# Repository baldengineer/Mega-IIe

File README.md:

# Golden Delicious
This project started as a portable Apple ][ by using the Mega-II chip from an IIGS. (This chip is precursor, and slightly different to the Gemini in the Mac LC compatibility card.) However, it evolved into making a miniture Apple IIe compatible computer.

This repo contains the KiCad design files, RP2040 firmware, and notes for the Mega IIe computer. 

## Rev 3 Video
This element14 Presents video documents the effort to get from an Applesoft Prompt to a fully functional computer, in a miniature case.

https://www.youtube.com/watch?v=gFCD4s_hsb4

You can find additional information on the [element14 Community](https://bald.ee/e14-megaiie) or in this [Hackster.io](https://www.hackster.io/news/bald-engineer-s-mega-iie-is-a-modern-miniature-apple-ii-based-on-mega-ii-chip-from-1986-019507d4d10c) article. 

## Bit Preserve
This project is why I started [Bit Preserve](https://github.com/baldengineer/bit-preserve), a project to archive vintage computer schematics.

# Notes
When live streaming the probject, I kept some notes here for future reference.

## (Off-)Stream Notes 2021-10-02
* Attempting to book the GD with a IIc ROM results in a lock-up.
  * graphics get initialized and the memory is dumped to the screen, but no beep and nothing past that.
  * Logic Analyzer suggests `BASICINIT` is doing a monitor version check in the F8 ROM, but failing. It calls a jump called `HANG`. Even though the 6502 should be jumping in a circle, it seems to keep doing other stuff. (Maybe it is just bus fetches that do nothing?)
* SLOTMAKER Bus Headers on the IO board are pinned out different from the SLOTMAKER Bus Header on the MEGA-65c02. For a ribbon cable, each pin-pair needs to be swapped, except for the last two. They are GND.

## Stream Notes 2021-10-01
Golden Delicious Rev 2 booted! Yay!

* \~DMA is wrong level
  * The two \`245 buffers have their enable pins connnected to \~DMA. I made the mistake of thinking that MEGA drove the \~DMA signal. That is not the case, nor does it make sense after thinking about it. For now, the \`245s have pin 19 lifted and tied to ground to always enable them. 
  * When connecting the IWM or a card to slotmaker, \~DMA situation needs to be resolved.

* [IIe / 6502 decoder](https://discord.com/channels/369243434080272385/843878836471201902/893914917676130314) for Waveforms / Digitial Discovery has been updated. 
* This [forum post](https://discord.com/channels/369243434080272385/843878836471201902/893915436620607488) has Digilent Waveforms beta builds that are downloadable without filling out the annoying registration form. (Or just use `asdf` for all of the fields.)

## Stream Notes 2021-06-02
* Wherefore no IIe ROM in the IIgs? Is it in the MEGA-II?
* [Warphammer: this seciton looks rommy](https://twitter.com/babbageboole/status/1001178057057566720/photo/1)
* rjhelms: that's the big question mark - there could be logic in the Mega II that never actually gets used because the CYA is doing it all in this implementation
* al: keep it all breakouts
* can we decode ROMEN1 and ROMEN2 ourselves?

## Stream Notes 2021-05-19
Things to look at on the scope:
* Composite signal out of the Mega II
* What is Mono-Color from VGC doing to Chroma into MC1377
* Is VGC refreshing apple II DRAM (or is it the Mega)
* why is the 28 MHz oscillator enabled/disabled from the VGC's !SYNC pin?
* [PLCC Pinout Page](https://www.sbprojects.net/knowledge/footprints/plcc/index.php)

### Renesas / IDT OSC: XLH735028.636360I 
* XL H 7 3 5 0 28.636360 I 
  * XL = 1,000,000 af
  * H = LVCMOS En/Dis Pin 1
  * 7 = 7.0 x 5.0 mm
  * 3 = 3.3 VDC
  * 5 = 100ppm for -40C to 105C only on tuesdays when the moon is full and it hasn't rained for a few days. also if you ate green skittles recently *Note1*

### BoM for Protoboards
* [Possible MC1377 Source](https://www.ebay.com/itm/192523168043?hash=item2cd346692b:g:BgIAAOSwWfda4kj6)

## Stream Notes 2021-05-16
* [WDC Application note on using 65C02 in Apple II and other old systems](https://www.westerndesigncenter.com/wdc/AN-002_W65C02S_Replacements.php)
* [65C02 Datasheet](https://www.westerndesigncenter.com/wdc/documentation/w65c02s.pdf)

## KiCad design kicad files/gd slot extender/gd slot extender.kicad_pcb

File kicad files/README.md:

## Golden Delicious KiCad Files

The Proto PCBs are boards to prototype an IIe from the IIgs ASICs. Eventually, these will be condensed to a single board.

### gd 6502 proto pcb
6502 board is designed for a WDC W65c02 with a QFP footprint. It has a single socket for an EPROM and is wired like the IIc's EEPROM. The `Address` and `Data` headers are meant to connect to the MEGA-II proto board. Other control signals are broken out to other headers.

Runs off of 5V.

### gd MegaII proto pcb
This board is the center piece. It contains the MEGA-II and has all of its signals broken out to multiple headers. 

It connects to both the VGC and 6502 boards. The VGC connects with a 40-pin cable, like an IDE cable. The 6502 connects with a couple of ribbon cables.

Runs off of 5V.

### gd VGC proto pcb
First board to be finished and the one with the least use for the final handheld. The VGC converts the RGB bitstream from the MEGA-II into an analog signal and then into NTSC.

The VGC also generates the 14 MHz clock from a 28 MHz oscilliator. (It is not clear yet which clocks the MEGA-II generates and which the VGC does.)

Runs off of +5V, -5V, and +12V. The 12V and -5V are used by the NTSC generation circuit.

### KiCad_Symbols
Late in the board creation process, I tried to consoliate the symbols into one location. These symbols and these boards are based off of the ROM3 IIgs schematic in [Bit Preserve](https://github.com/baldengineer/bit-preserve).

### MegaII Breakout
Very old breakout board. Created that and realized it wasn't very useful by itself.

## Live Stream
This entire project has been livestreamed on [Bald Engineer Live](https://twitch.tv/baldengineer).

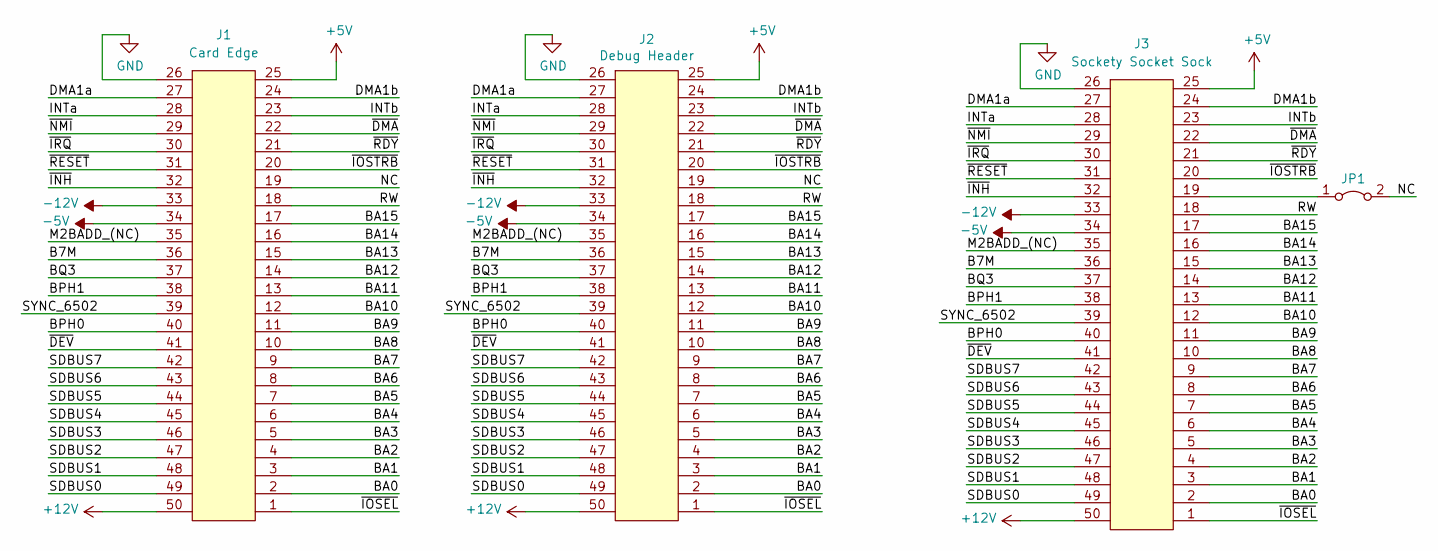
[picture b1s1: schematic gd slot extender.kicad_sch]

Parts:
J1: Card Edge; AppleIIBus
J2: Debug Header; PinHeader_2x25_P2.54mm_Vertical
J3: Sockety Socket Sock; Amp_2358256-4_50pos_right_angle_card
JP1: Jumper_2_Bridged; SolderJumper-2_P1.3mm_Bridged_RoundedPad1.0x1.5mm

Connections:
+5V: J1.25, J2.25, J3.25
+12V: J1.50, J2.50, J3.50
-5V: J1.34, J2.34, J3.34
-12V: J1.33, J2.33, J3.33
/B7M: J1.36, J2.36, J3.36
/BA0: J1.2, J2.2, J3.2
/BA1: J1.3, J2.3, J3.3
/BA2: J1.4, J2.4, J3.4
/BA3: J1.5, J2.5, J3.5
/BA4: J1.6, J2.6, J3.6
/BA5: J1.7, J2.7, J3.7
/BA6: J1.8, J2.8, J3.8
/BA7: J1.9, J2.9, J3.9
/BA8: J1.10, J2.10, J3.10
/BA9: J1.11, J2.11, J3.11
/BA10: J1.12, J2.12, J3.12
/BA11: J1.13, J2.13, J3.13
/BA12: J1.14, J2.14, J3.14
/BA13: J1.15, J2.15, J3.15
/BA14: J1.16, J2.16, J3.16
/BA15: J1.17, J2.17, J3.17
/BPH0: J1.40, J2.40, J3.40
/BPH1: J1.38, J2.38, J3.38
/BQ3: J1.37, J2.37, J3.37
/DMA1a: J1.27, J2.27, J3.27
/DMA1b: J1.24, J2.24, J3.24
/INTa: J1.28, J2.28, J3.28
/INTb: J1.23, J2.23, J3.23
/M2BADD_(NC): J1.35, J2.35, J3.35
/NC: J1.19, J2.19, JP1.2 (B)
/RW: J1.18, J2.18, J3.18
/SDBUS0: J1.49, J2.49, J3.49
/SDBUS1: J1.48, J2.48, J3.48
/SDBUS2: J1.47, J2.47, J3.47
/SDBUS3: J1.46, J2.46, J3.46
/SDBUS4: J1.45, J2.45, J3.45
/SDBUS5: J1.44, J2.44, J3.44
/SDBUS6: J1.43, J2.43, J3.43
/SDBUS7: J1.42, J2.42, J3.42
/SYNC_6502: J1.39, J2.39, J3.39
/~DEV: J1.41, J2.41, J3.41
/~DMA: J1.22, J2.22, J3.22
/~INH: J1.32, J2.32, J3.32
/~IOSEL: J1.1, J2.1, J3.1
/~IOSTRB: J1.20, J2.20, J3.20
/~IRQ: J1.30, J2.30, J3.30
/~NMI: J1.29, J2.29, J3.29
/~RDY: J1.21, J2.21, J3.21
/~RESET: J1.31, J2.31, J3.31
GND: J1.26, J2.26, J3.26
unnamed: J3.19, JP1.1 (A)

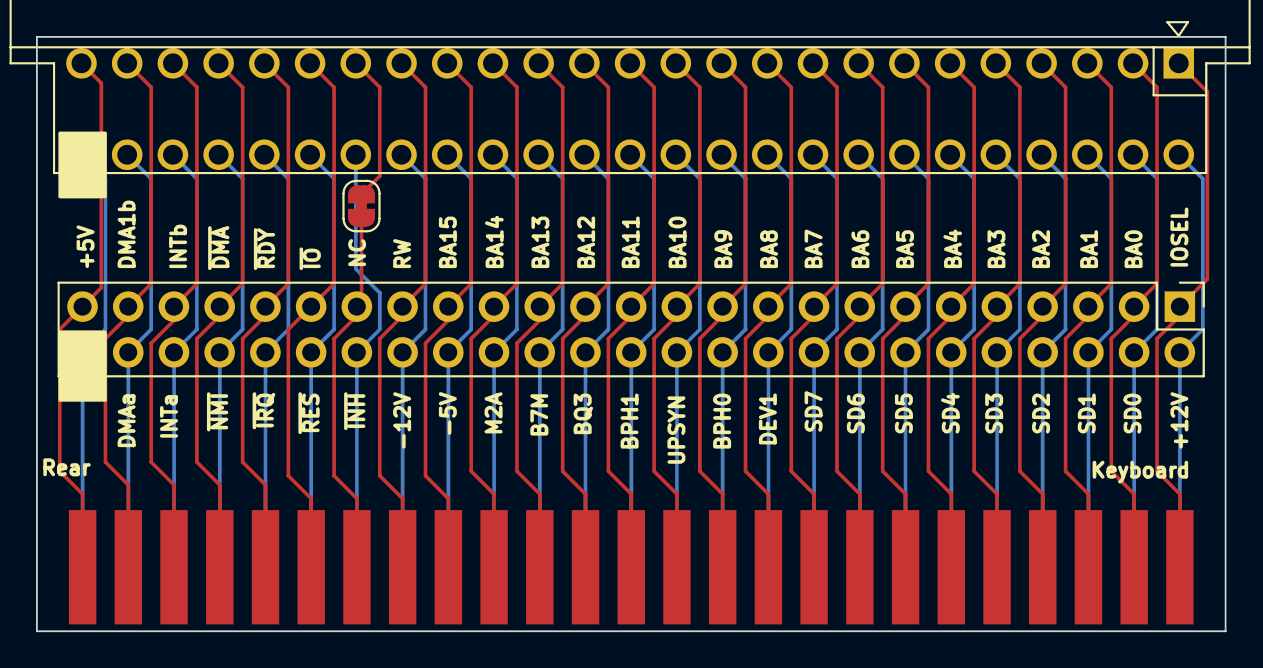
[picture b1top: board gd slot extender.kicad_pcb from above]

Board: 2 copper layers, 66.0 x 33.0 mm, 4 parts (0 on the bottom side), 51 nets.

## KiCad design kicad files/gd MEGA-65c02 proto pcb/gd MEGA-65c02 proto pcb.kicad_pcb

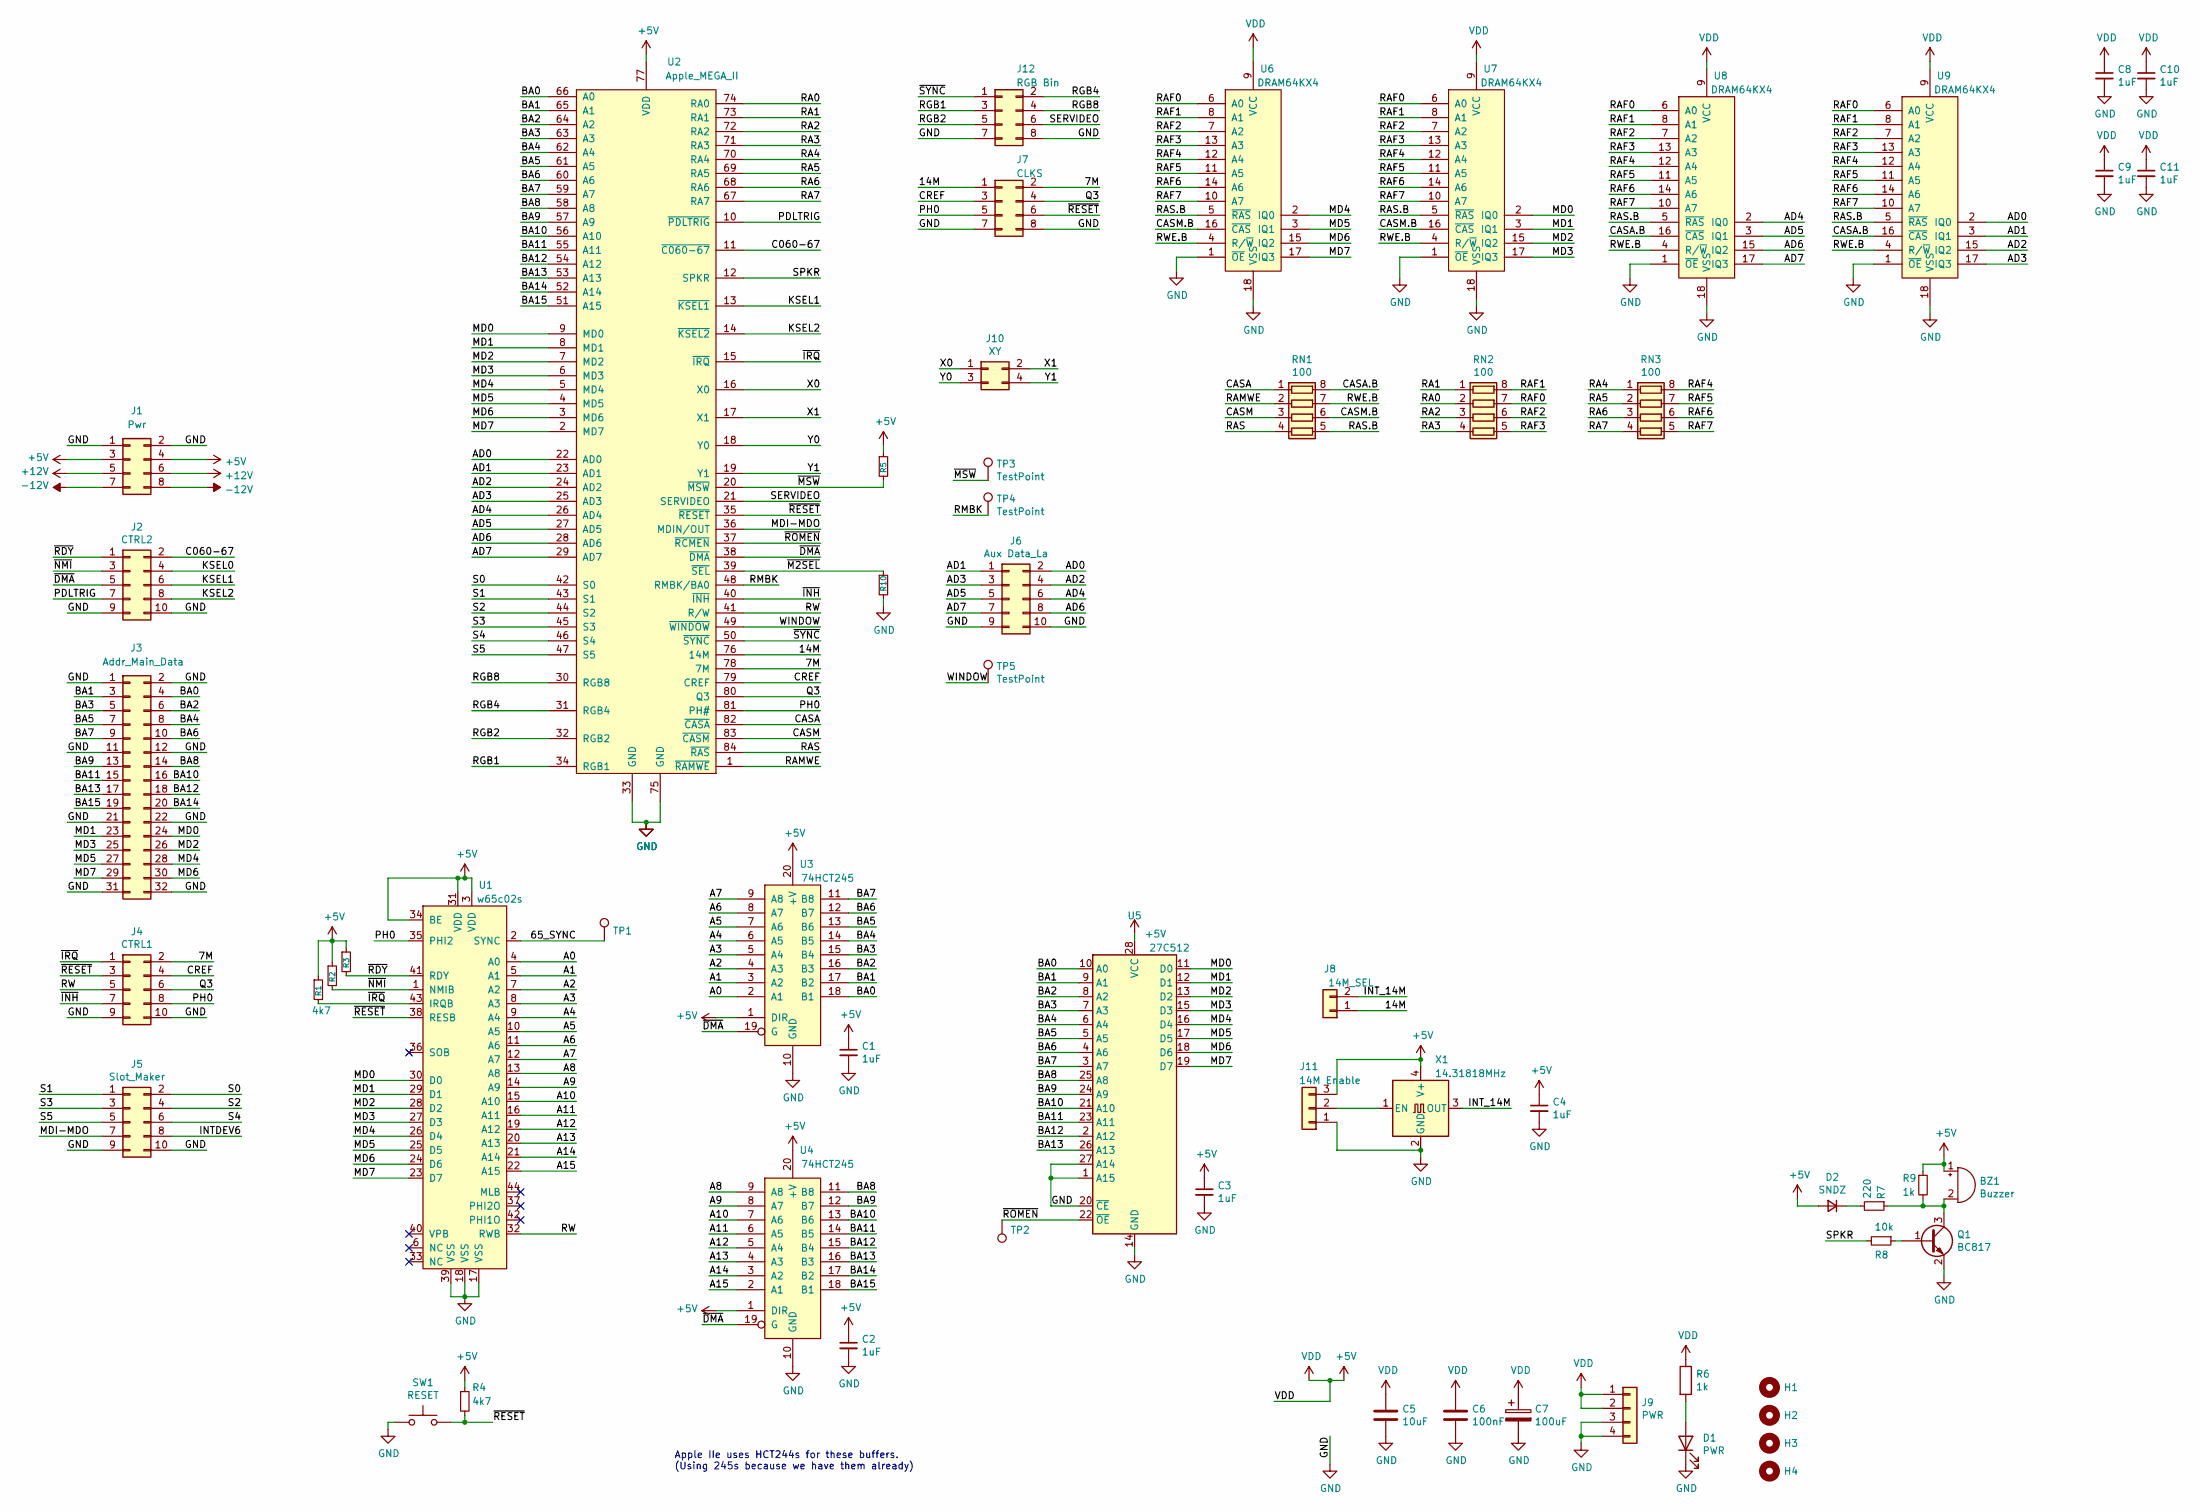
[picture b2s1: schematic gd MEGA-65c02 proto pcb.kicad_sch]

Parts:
BZ1: Buzzer; 12mm_Piezo_Buzzer
C1, C2, C3, C4, C8, C9, C10, C11: 1uF; C_0805_2012Metric
C5: 10uF; C_0805_2012Metric
C6: 100nF; C_0805_2012Metric
C7: 100uF; CP_EIA-3216-18_Kemet-A_Pad1.58x1.35mm_HandSolder
D1: PWR; LED_1206_3216Metric
D2: SNDZ; LED_1206_3216Metric
H1, H2, H3, H4: MountingHole; MountingHole_2.5mm
J1: Pwr; PinHeader_2x04_P2.54mm_Vertical-NOSILK
J2: CTRL2; PinHeader_2x05_P2.54mm_Vertical
J3: Addr_Main_Data; PinHeader_2x16_P2.54mm_Vertical
J4: CTRL1; PinHeader_2x05_P2.54mm_Vertical
J5: Slot_Maker; PinHeader_2x05_P2.54mm_Vertical
J6: Aux Data_La; PinHeader_2x05_P2.54mm_Vertical
J7: CLKS; PinHeader_2x04_P2.54mm_Vertical
J8: 14M_SEL; PinHeader_1x02_P2.54mm_Vertical
J9: PWR; PinHeader_1x04_P2.54mm_Vertical
J10: XY; PinHeader_2x02_P2.54mm_Vertical
J11: 14M Enable; PinHeader_1x03_P2.54mm_Vertical
J12: RGB Bin; PinHeader_2x04_P2.54mm_Vertical
Q1: BC817; SOT-23
R1, R4, R5, R10: 4k7; R_0805_2012Metric
R2, R3: 3k3; R_0805_2012Metric
R6, R9: 1k; R_0805_2012Metric
R7: 220; R_0805_2012Metric
R8: 10k; R_0805_2012Metric
RN1, RN2, RN3: 100; R_Array_Convex_4x0612
SW1: RESET; SW_Push_1P1T_NO_CK_KSC6xxJ
TP1, TP2: TestPoint_Harwin; Harwin-S1751-46-Test-Point
TP3, TP4, TP5: TestPoint; Harwin-S1751-46-Test-Point
U1: w65c02s; TQFP-44_10x10mm_P0.8mm
U2: Apple_MEGA_II; PLCC-84_THT-Socket
U3, U4: 74HCT245; SOIC-20W_7.5x12.8mm_P1.27mm
U5: 27C512; DIP_Socket-28_W11.9_W12.7_W15.24_W17.78_W18.5_3M_228-1277-0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
U6, U7, U8, U9: DRAM64KX4; DIP-18_W7.62mm_Socket_LongPads
X1: 14.31818MHz; Oscillator_SMD_SeikoEpson_SG8002CA-4Pin_7.0x5.0mm_HandSolde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; MPN MCSJK-6NC1-14.31818-25-B

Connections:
+5V: BZ1.1 (-), C1.1, C2.1, C3.1, C4.1, C5.1, C6.1, C7.1, C8.1, C9.1, C10.1, C11.1, D2.2 (A), J1.3, J1.4, J9.1, J9.2, J11.3, R1.1, R2.1, R3.1, R4.1, R5.1, R6.1, R9.1, U1.3 (VDD), U1.31 (VDD), U1.34 (BE), U2.77 (VDD), U3.1 (DIR), U3.20 (+V), U4.1 (DIR), U4.20 (+V), U5.28 (VCC), U6.9 (VCC), U7.9 (VCC), U8.9 (VCC), U9.9 (VCC), X1.4 (V+)
+12V: J1.5, J1.6
-12V: J1.7, J1.8
/7M: J4.2, J7.2, U2.78 (7M)
/14M: J7.1, J8.1, U2.76 (14M)
/65_SYNC: TP1.1, U1.2 (SYNC)
/A0: U1.4 (A0), U3.2 (A1)
/A1: U1.5 (A1), U3.3 (A2)
/A2: U1.7 (A2), U3.4 (A3)
/A3: U1.8 (A3), U3.5 (A4)
/A4: U1.9 (A4), U3.6 (A5)
/A5: U1.10 (A5), U3.7 (A6)
/A6: U1.11 (A6), U3.8 (A7)
/A7: U1.12 (A7), U3.9 (A8)
/A8: U1.13 (A8), U4.9 (A8)
/A9: U1.14 (A9), U4.8 (A7)
/A10: U1.15 (A10), U4.7 (A6)
/A11: U1.16 (A11), U4.6 (A5)
/A12: U1.19 (A12), U4.5 (A4)
/A13: U1.20 (A13), U4.4 (A3)
/A14: U1.21 (A14), U4.3 (A2)
/A15: U1.22 (A15), U4.2 (A1)
/AD0: J6.2, U2.22 (AD0), U9.2 (IQ0)
/AD1: J6.1, U2.23 (AD1), U9.3 (IQ1)
/AD2: J6.4, U2.24 (AD2), U9.15 (IQ2)
/AD3: J6.3, U2.25 (AD3), U9.17 (IQ3)
/AD4: J6.6, U2.26 (AD4), U8.2 (IQ0)
/AD5: J6.5, U2.27 (AD5), U8.3 (IQ1)
/AD6: J6.8, U2.28 (AD6), U8.15 (IQ2)
/AD7: J6.7, U2.29 (AD7), U8.17 (IQ3)
/BA0: J3.4, U2.66 (A0), U3.18 (B1), U5.10 (A0)
/BA1: J3.3, U2.65 (A1), U3.17 (B2), U5.9 (A1)
/BA2: J3.6, U2.64 (A2), U3.16 (B3), U5.8 (A2)
/BA3: J3.5, U2.63 (A3), U3.15 (B4), U5.7 (A3)
/BA4: J3.8, U2.62 (A4), U3.14 (B5), U5.6 (A4)
/BA5: J3.7, U2.61 (A5), U3.13 (B6), U5.5 (A5)
/BA6: J3.10, U2.60 (A6), U3.12 (B7), U5.4 (A6)
/BA7: J3.9, U2.59 (A7), U3.11 (B8), U5.3 (A7)
/BA8: J3.14, U2.58 (A8), U4.11 (B8), U5.25 (A8)
/BA9: J3.13, U2.57 (A9), U4.12 (B7), U5.24 (A9)
/BA10: J3.16, U2.56 (A10), U4.13 (B6), U5.21 (A10)
/BA11: J3.15, U2.55 (A11), U4.14 (B5), U5.23 (A11)
/BA12: J3.18, U2.54 (A12), U4.15 (B4), U5.2 (A12)
/BA13: J3.17, U2.53 (A13), U4.16 (B3), U5.26 (A13)
/BA14: J3.20, U2.52 (A14), U4.17 (B2)
/BA15: J3.19, U2.51 (A15), U4.18 (B1)
/C060-67: J2.2, U2.11 (~C060-67)
/CASA: RN1.1 (R1.1), U2.82 (~CASA)
/CASA.B: RN1.8 (R1.2), U8.16 (~CAS), U9.16 (~CAS)
/CASM: RN1.3 (R3.1), U2.83 (~CASM)
/CASM.B: RN1.6 (R3.2), U6.16 (~CAS), U7.16 (~CAS)
/CREF: J4.4, J7.3, U2.79 (CREF)
/INTDEV6: J5.8
/INT_14M: J8.2, X1.3 (OUT)
/KSEL0: J2.4
/KSEL1: J2.6, U2.13 (~KSEL1)
/KSEL2: J2.8, U2.14 (~KSEL2)
/MD0: J3.24, U1.30 (D0), U2.9 (MD0), U5.11 (D0), U7.2 (IQ0)
/MD1: J3.23, U1.29 (D1), U2.8 (MD1), U5.12 (D1), U7.3 (IQ1)
/MD2: J3.26, U1.28 (D2), U2.7 (MD2), U5.13 (D2), U7.15 (IQ2)
/MD3: J3.25, U1.27 (D3), U2.6 (MD3), U5.15 (D3), U7.17 (IQ3)
/MD4: J3.28, U1.26 (D4), U2.5 (MD4), U5.16 (D4), U6.2 (IQ0)
/MD5: J3.27, U1.25 (D5), U2.4 (MD5), U5.17 (D5), U6.3 (IQ1)
/MD6: J3.30, U1.24 (D6), U2.3 (MD6), U5.18 (D6), U6.15 (IQ2)
/MD7: J3.29, U1.23 (D7), U2.2 (MD7), U5.19 (D7), U6.17 (IQ3)
/MDI-MDO: J5.7, U2.36 (MDIN/OUT)
/PDLTRIG: J2.7, U2.10 (~PDLTRIG)
/PH0: J4.8, J7.5, U1.35 (PHI2), U2.81 (PH#)
/Q3: J4.6, J7.4, U2.80 (Q3)
/RA0: RN2.2 (R2.1), U2.74 (RA0)
/RA1: RN2.1 (R1.1), U2.73 (RA1)
/RA2: RN2.3 (R3.1), U2.72 (RA2)
/RA3: RN2.4 (R4.1), U2.71 (RA3)
/RA4: RN3.1 (R1.1), U2.70 (RA4)
/RA5: RN3.2 (R2.1), U2.69 (RA5)
/RA6: RN3.3 (R3.1), U2.68 (RA6)
/RA7: RN3.4 (R4.1), U2.67 (RA7)
/RAF0: RN2.7 (R2.2), U6.6 (A0), U7.6 (A0), U8.6 (A0), U9.6 (A0)
/RAF1: RN2.8 (R1.2), U6.8 (A1), U7.8 (A1), U8.8 (A1), U9.8 (A1)
/RAF2: RN2.6 (R3.2), U6.7 (A2), U7.7 (A2), U8.7 (A2), U9.7 (A2)
/RAF3: RN2.5 (R4.2), U6.13 (A3), U7.13 (A3), U8.13 (A3), U9.13 (A3)
/RAF4: RN3.8 (R1.2), U6.12 (A4), U7.12 (A4), U8.12 (A4), U9.12 (A4)
/RAF5: RN3.7 (R2.2), U6.11 (A5), U7.11 (A5), U8.11 (A5), U9.11 (A5)
/RAF6: RN3.6 (R3.2), U6.14 (A6), U7.14 (A6), U8.14 (A6), U9.14 (A6)
/RAF7: RN3.5 (R4.2), U6.10 (A7), U7.10 (A7), U8.10 (A7), U9.10 (A7)
/RAMWE: RN1.2 (R2.1), U2.1 (~RAMWE)
/RAS: RN1.4 (R4.1), U2.84 (~RAS)
/RAS.B: RN1.5 (R4.2), U6.5 (~RAS), U7.5 (~RAS), U8.5 (~RAS), U9.5 (~RAS)
/RGB1: J12.3, U2.34 (RGB1)
/RGB2: J12.5, U2.32 (RGB2)
/RGB4: J12.2, U2.31 (RGB4)
/RGB8: J12.4, U2.30 (RGB8)
/RMBK: TP4.1, U2.48 (RMBK/BA0)
/RW: J4.5, U1.32 (RWB), U2.41 (R/W)
/RWE.B: RN1.7 (R2.2), U6.4 (R/~W), U7.4 (R/~W), U8.4 (R/~W), U9.4 (R/~W)
/S0: J5.2, U2.42 (S0)
/S1: J5.1, U2.43 (S1)
/S2: J5.4, U2.44 (S2)
/S3: J5.3, U2.45 (S3)
/S4: J5.6, U2.46 (S4)
/S5: J5.5, U2.47 (S5)
/SERVIDEO: J12.6, U2.21 (SERVIDEO)
/SPKR: R8.2, U2.12 (SPKR)
/WINDOW: TP5.1, U2.49 (~WINDOW)
/X0: J10.1, U2.16 (X0)
/X1: J10.2, U2.17 (X1)
/Y0: J10.3, U2.18 (Y0)
/Y1: J10.4, U2.19 (Y1)
/~DMA: J2.5, U2.38 (~DMA), U3.19 (G), U4.19 (G)
/~INH: J4.7, U2.40 (~INH)
/~IRQ: J4.1, R1.2, U1.43 (IRQB), U2.15 (~IRQ)
/~M2SEL: R10.1, U2.39 (~SEL)
/~MSW: R5.2, TP3.1, U2.20 (~MSW)
/~NMI: J2.3, R2.2, U1.1 (NMIB)
/~RDY: J2.1, R3.2, U1.41 (RDY)
/~RESET: J4.3, J7.6, R4.2, SW1.2, U1.38 (RESB), U2.35 (~RESET)
/~ROMEN: TP2.1, U2.37 (~RCMEN), U5.22 (~OE)
/~SYNC: J12.1, U2.50 (~SYNC)
GND: C1.2, C2.2, C3.2, C4.2, C5.2, C6.2, C7.2, C8.2, C9.2, C10.2, C11.2, D1.1 (K), J1.1, J1.2, J2.9, J2.10, J3.1, J3.2, J3.11, J3.12, J3.21, J3.22, J3.31, J3.32, J4.9, J4.10, J5.9, J5.10, J6.9, J6.10, J7.7, J7.8, J9.3, J9.4, J11.1, J12.7, J12.8, Q1.2 (E), R10.2, SW1.1, U1.17 (VSS), U1.18 (VSS), U1.39 (VSS), U2.33 (GND), U2.75 (GND), U3.10 (GND), U4.10 (GND), U5.1 (A15), U5.14 (GND), U5.20 (~CE), U5.27 (A14), U6.1 (~OE), U6.18 (VSS), U7.1 (~OE), U7.18 (VSS), U8.1 (~OE), U8.18 (VSS), U9.1 (~OE), U9.18 (VSS), X1.2 (GND)
unnamed: BZ1.2 (+), Q1.3 (C), R7.1, R9.2
unnamed: D1.2 (A), R6.2
unnamed: D2.1 (K), R7.2
unnamed: J11.2, X1.1 (EN)
unnamed: Q1.1 (B), R8.1

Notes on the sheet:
Apple IIe uses HCT244s for these buffers. (Using 245s because we have them already)

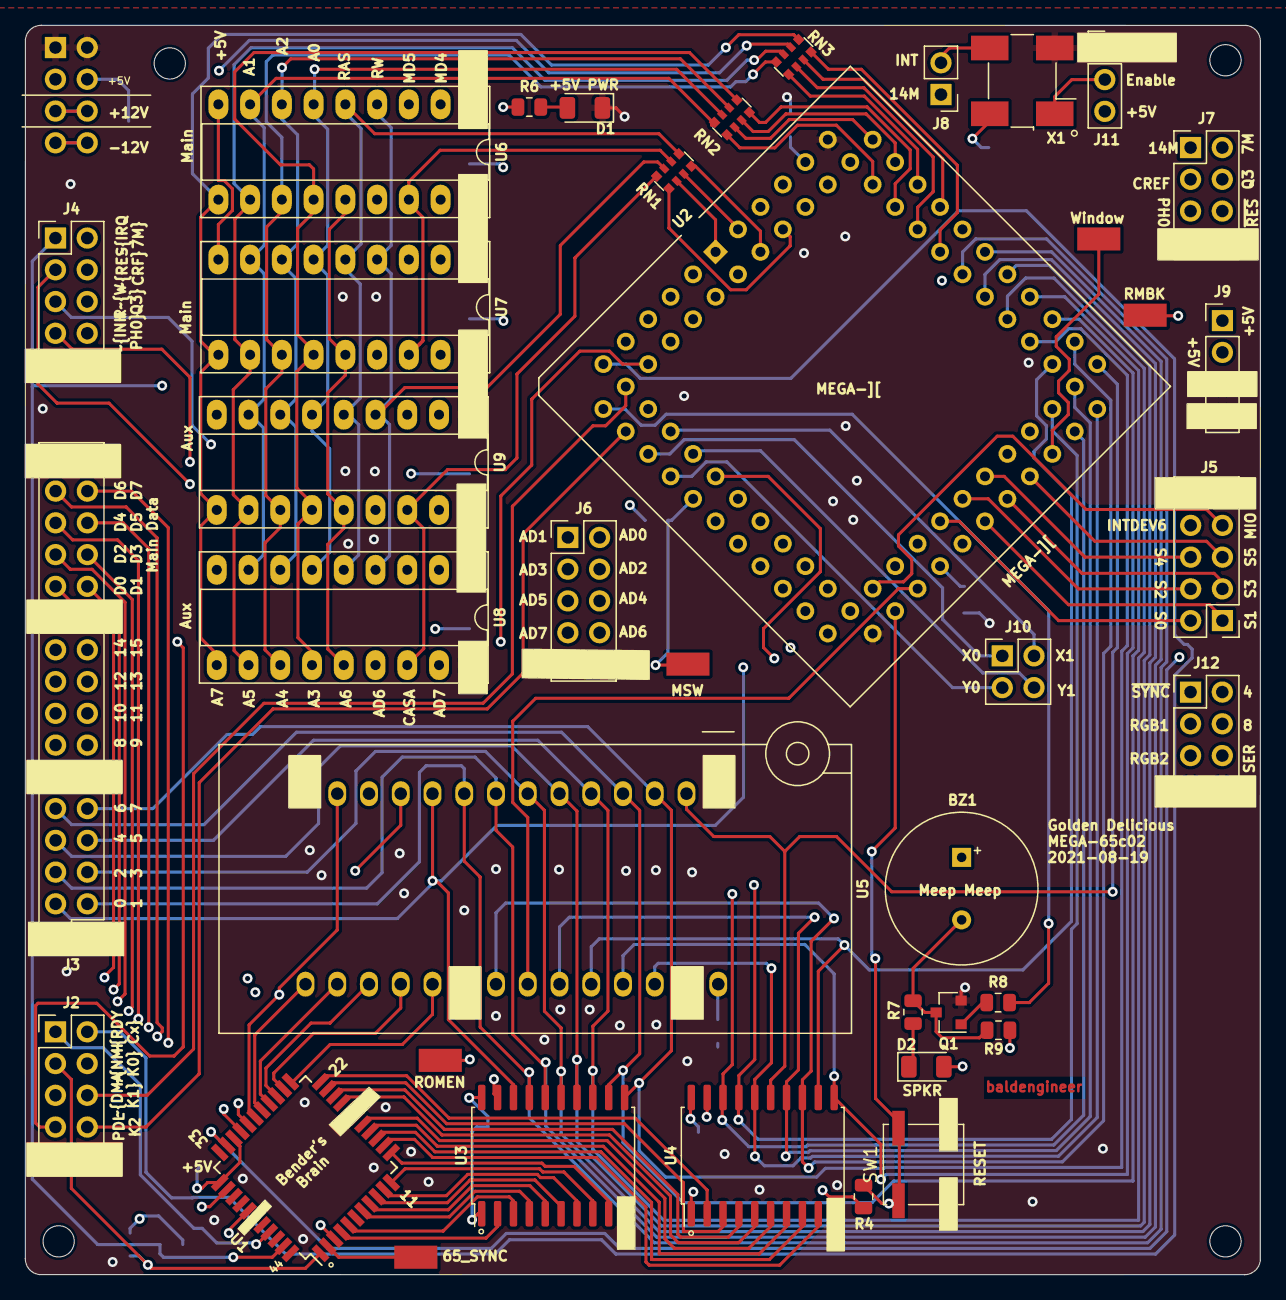
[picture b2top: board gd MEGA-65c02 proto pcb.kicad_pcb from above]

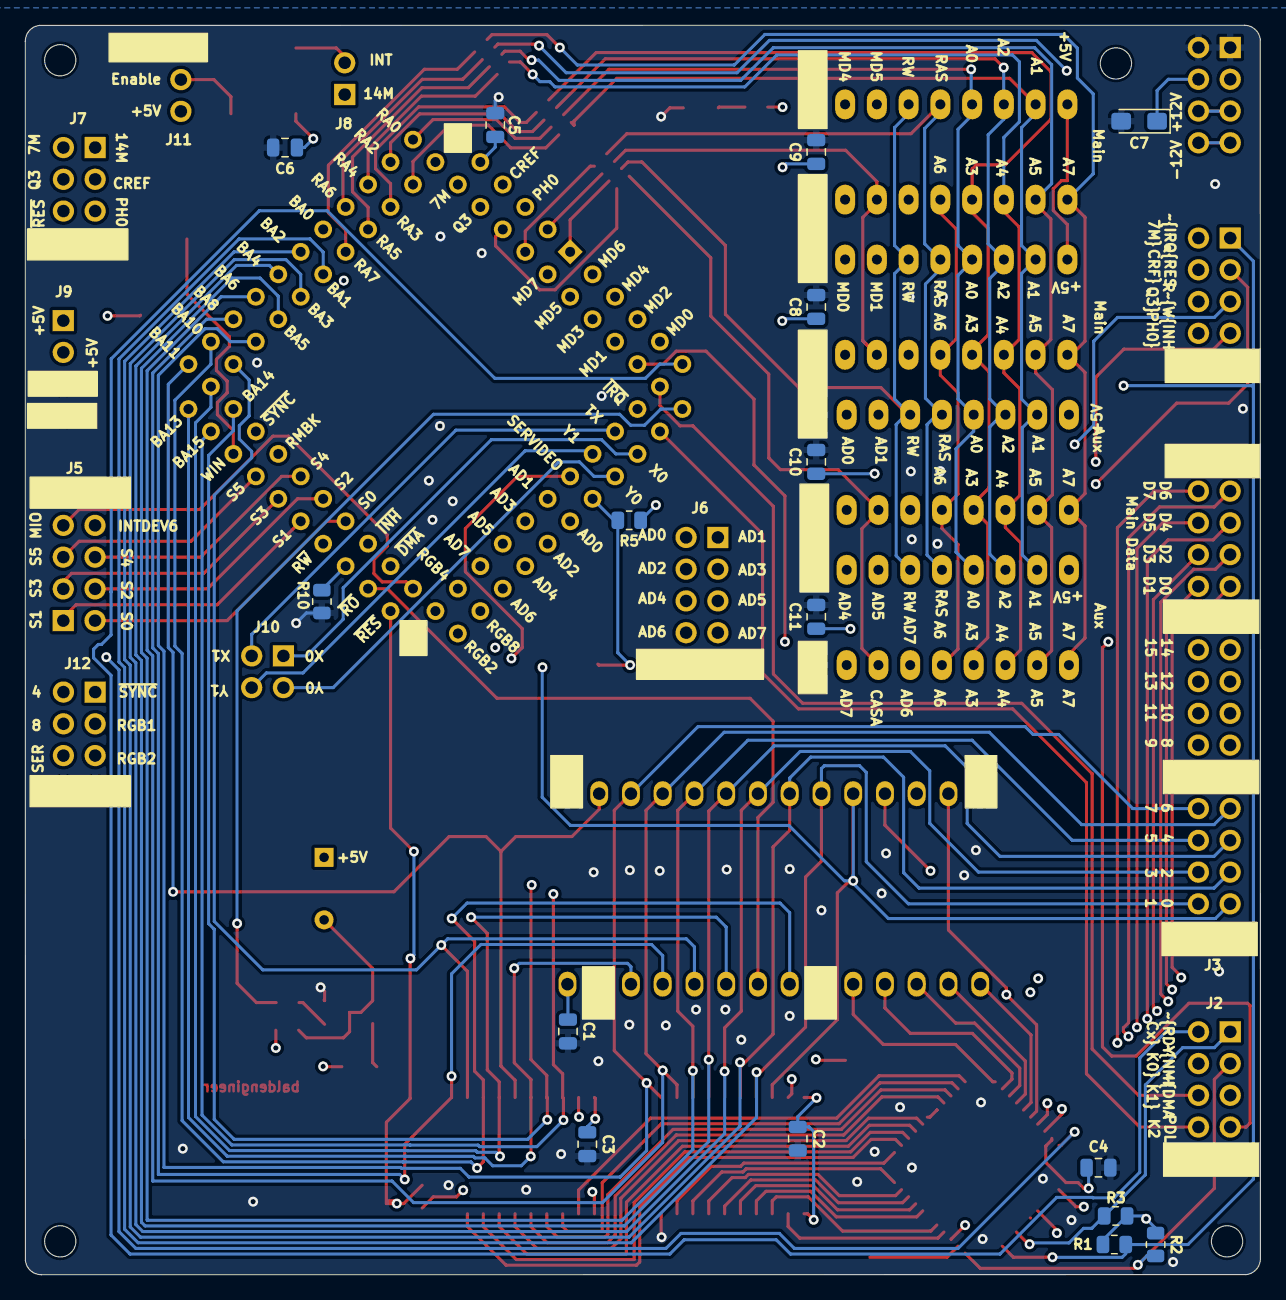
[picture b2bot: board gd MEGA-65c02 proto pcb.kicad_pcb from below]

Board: 4 copper layers, 98.8 x 99.9 mm, 60 parts (16 on the bottom side), 122 nets.

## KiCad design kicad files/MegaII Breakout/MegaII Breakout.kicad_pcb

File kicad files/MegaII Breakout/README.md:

I quickly realized the MEGA-II by itself wasn't going to be a useful breakout. 

So, this board got replaced by the "gd MEGA-II" proto board.

(During KiCad 7 update, multiple symbols were lost. I tried to fix them, but the most recent schematic was not the one used for the pcb!)

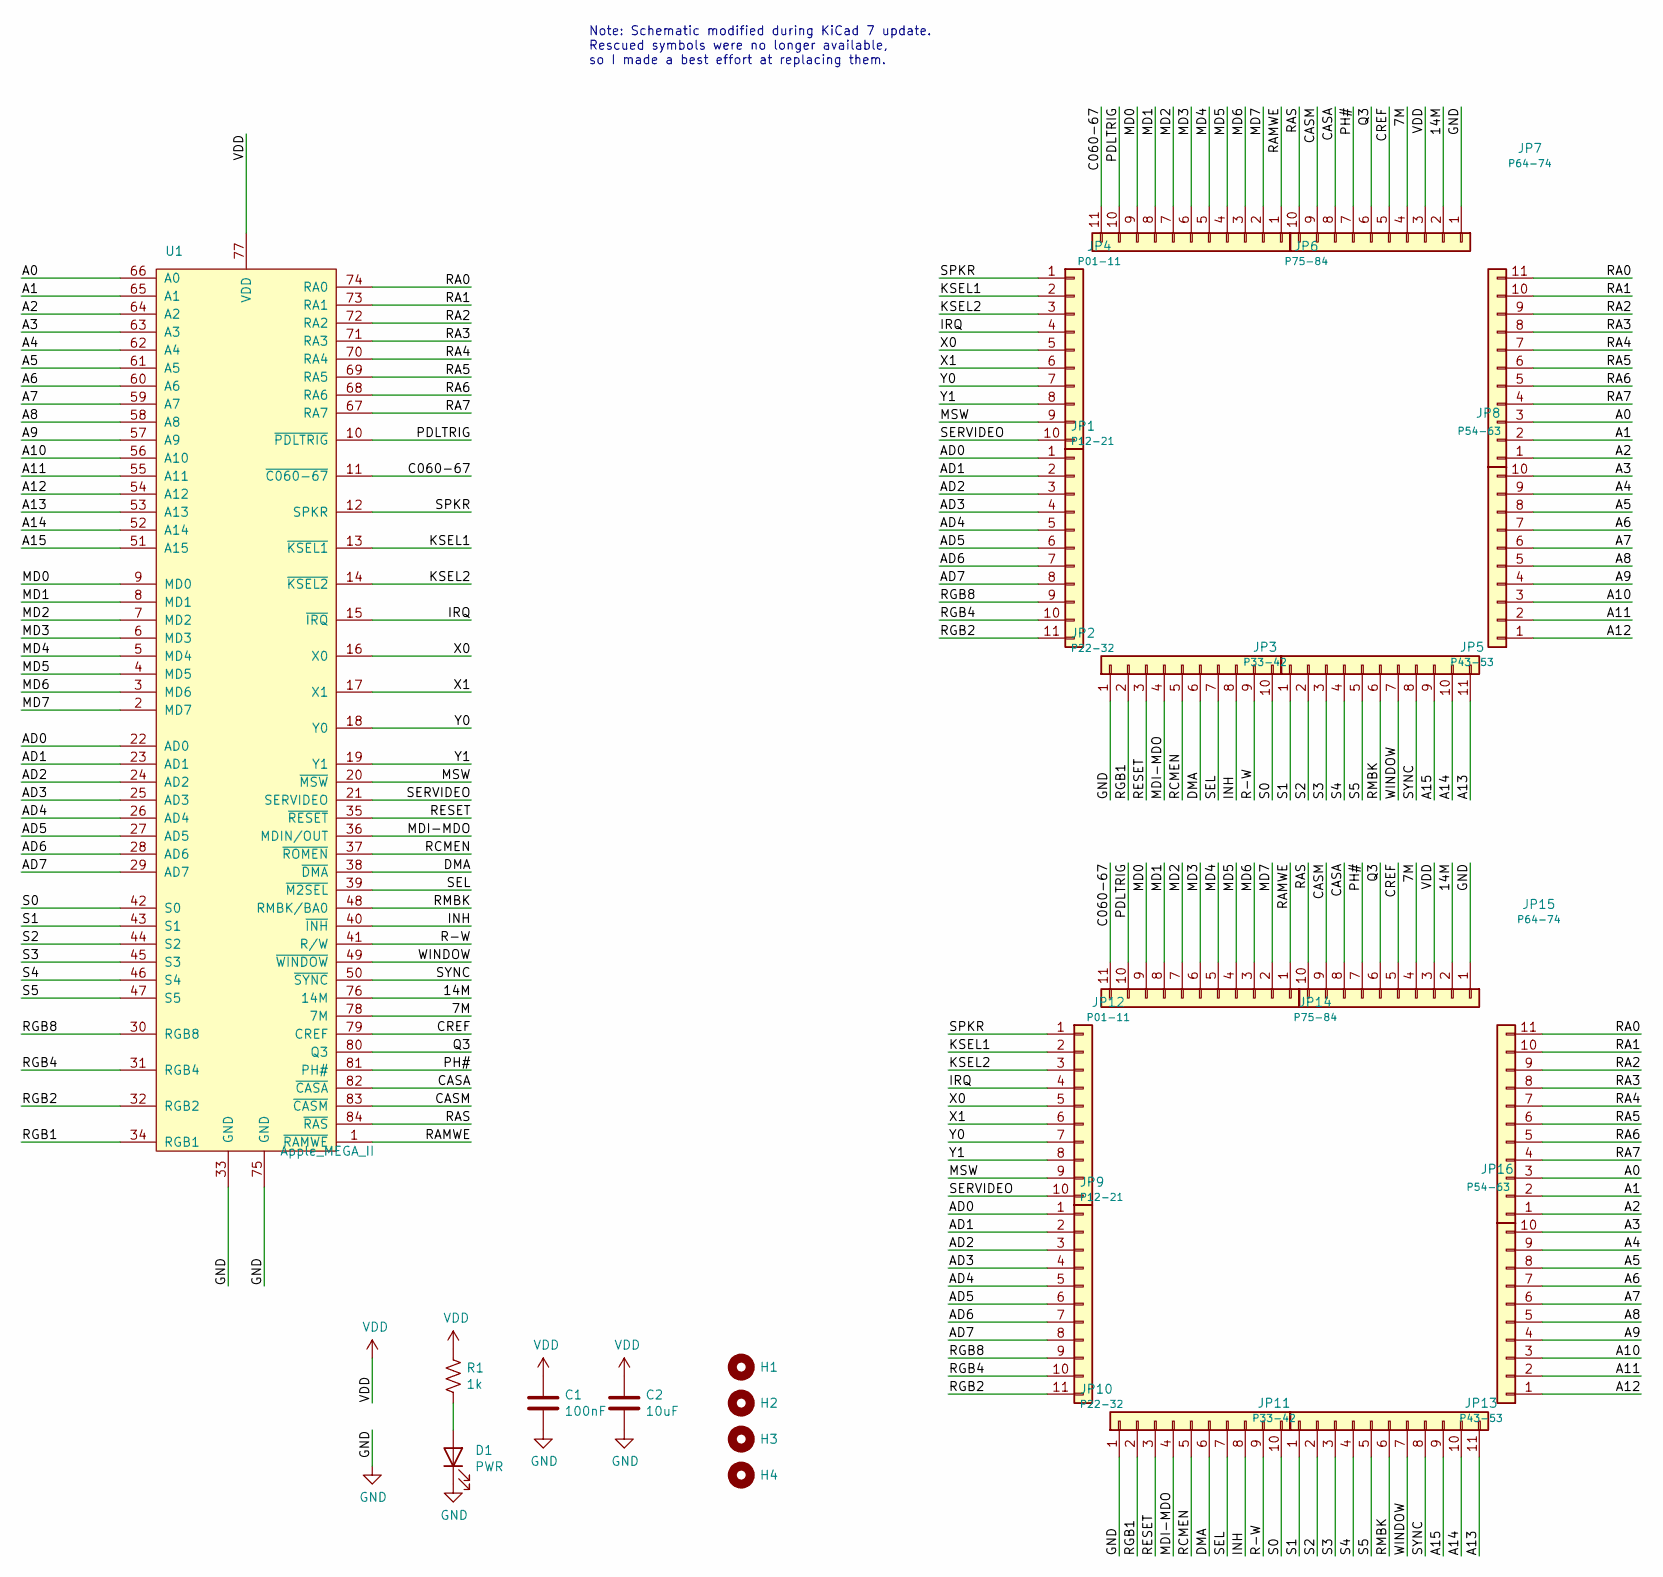
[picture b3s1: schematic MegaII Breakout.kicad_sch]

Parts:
C1: 100nF; C_0805_2012Metric
C2: 10uF; C_0805_2012Metric
D1: PWR; LED_1206_3216Metric
H1, H2, H3, H4: MountingHole; MountingHole_2.5mm
JP1, JP9: P12-21; PinHeader_1x10_P2.54mm_Vertical
JP2, JP10: P22-32; PinHeader_1x11_P2.54mm_Vertical
JP3, JP11: P33-42; PinHeader_1x10_P2.54mm_Vertical
JP4, JP12: P01-11; PinHeader_1x11_P2.54mm_Vertical
JP5, JP13: P43-53; PinHeader_1x11_P2.54mm_Vertical
JP6, JP14: P75-84; PinHeader_1x10_P2.54mm_Vertical
JP7, JP15: P64-74; PinHeader_1x11_P2.54mm_Vertical
JP8, JP16: P54-63; PinHeader_1x10_P2.54mm_Vertical
R1: 1k; R_0805_2012Metric
U1: Apple_MEGA_II; PLCC-84_THT-Socket

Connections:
/7M: JP6.4, JP14.4, U1.78 (7M)
/14M: JP6.2, JP14.2, U1.76 (14M)
/A0: JP7.3, JP15.3, U1.66 (A0)
/A1: JP7.2, JP15.2, U1.65 (A1)
/A2: JP7.1, JP15.1, U1.64 (A2)
/A3: JP8.10, JP16.10, U1.63 (A3)
/A4: JP8.9, JP16.9, U1.62 (A4)
/A5: JP8.8, JP16.8, U1.61 (A5)
/A6: JP8.7, JP16.7, U1.60 (A6)
/A7: JP8.6, JP16.6, U1.59 (A7)
/A8: JP8.5, JP16.5, U1.58 (A8)
/A9: JP8.4, JP16.4, U1.57 (A9)
/A10: JP8.3, JP16.3, U1.56 (A10)
/A11: JP8.2, JP16.2, U1.55 (A11)
/A12: JP8.1, JP16.1, U1.54 (A12)
/A13: JP5.11, JP13.11, U1.53 (A13)
/A14: JP5.10, JP13.10, U1.52 (A14)
/A15: JP5.9, JP13.9, U1.51 (A15)
/AD0: JP2.1, JP10.1, U1.22 (AD0)
/AD1: JP2.2, JP10.2, U1.23 (AD1)
/AD2: JP2.3, JP10.3, U1.24 (AD2)
/AD3: JP2.4, JP10.4, U1.25 (AD3)
/AD4: JP2.5, JP10.5, U1.26 (AD4)
/AD5: JP2.6, JP10.6, U1.27 (AD5)
/AD6: JP2.7, JP10.7, U1.28 (AD6)
/AD7: JP2.8, JP10.8, U1.29 (AD7)
/C060-67: JP4.11, JP12.11, U1.11 (~C060-67)
/CASA: JP6.8, JP14.8, U1.82 (~CASA)
/CASM: JP6.9, JP14.9, U1.83 (~CASM)
/CREF: JP6.5, JP14.5, U1.79 (CREF)
/DMA: JP3.6, JP11.6, U1.38 (~DMA)
/INH: JP3.8, JP11.8, U1.40 (~INH)
/IRQ: JP1.4, JP9.4, U1.15 (~IRQ)
/KSEL1: JP1.2, JP9.2, U1.13 (~KSEL1)
/KSEL2: JP1.3, JP9.3, U1.14 (~KSEL2)
/MD0: JP4.9, JP12.9, U1.9 (MD0)
/MD1: JP4.8, JP12.8, U1.8 (MD1)
/MD2: JP4.7, JP12.7, U1.7 (MD2)
/MD3: JP4.6, JP12.6, U1.6 (MD3)
/MD4: JP4.5, JP12.5, U1.5 (MD4)
/MD5: JP4.4, JP12.4, U1.4 (MD5)
/MD6: JP4.3, JP12.3, U1.3 (MD6)
/MD7: JP4.2, JP12.2, U1.2 (MD7)
/MDI-MDO: JP3.4, JP11.4, U1.36 (MDIN/OUT)
/MSW: JP1.9, JP9.9, U1.20 (~MSW)
/PDLTRIG: JP4.10, JP12.10, U1.10 (~PDLTRIG)
/PH#: JP6.7, JP14.7, U1.81 (PH#)
/Q3: JP6.6, JP14.6, U1.80 (Q3)
/R-W: JP3.9, JP11.9, U1.41 (R/W)
/RA0: JP7.11, JP15.11, U1.74 (RA0)
/RA1: JP7.10, JP15.10, U1.73 (RA1)
/RA2: JP7.9, JP15.9, U1.72 (RA2)
/RA3: JP7.8, JP15.8, U1.71 (RA3)
/RA4: JP7.7, JP15.7, U1.70 (RA4)
/RA5: JP7.6, JP15.6, U1.69 (RA5)
/RA6: JP7.5, JP15.5, U1.68 (RA6)
/RA7: JP7.4, JP15.4, U1.67 (RA7)
/RAMWE: JP4.1, JP12.1, U1.1 (~RAMWE)
/RAS: JP6.10, JP14.10, U1.84 (~RAS)
/RCMEN: JP3.5, JP11.5, U1.37 (~ROMEN)
/RESET: JP3.3, JP11.3, U1.35 (~RESET)
/RGB1: JP3.2, JP11.2, U1.34 (RGB1)
/RGB2: JP2.11, JP10.11, U1.32 (RGB2)
/RGB4: JP2.10, JP10.10, U1.31 (RGB4)
/RGB8: JP2.9, JP10.9, U1.30 (RGB8)
/RMBK: JP5.6, JP13.6, U1.48 (RMBK/BA0)
/S0: JP3.10, JP11.10, U1.42 (S0)
/S1: JP5.1, JP13.1, U1.43 (S1)
/S2: JP5.2, JP13.2, U1.44 (S2)
/S3: JP5.3, JP13.3, U1.45 (S3)
/S4: JP5.4, JP13.4, U1.46 (S4)
/S5: JP5.5, JP13.5, U1.47 (S5)
/SEL: JP3.7, JP11.7, U1.39 (~M2SEL)
/SERVIDEO: JP1.10, JP9.10, U1.21 (SERVIDEO)
/SPKR: JP1.1, JP9.1, U1.12 (SPKR)
/SYNC: JP5.8, JP13.8, U1.50 (~SYNC)
/WINDOW: JP5.7, JP13.7, U1.49 (~WINDOW)
/X0: JP1.5, JP9.5, U1.16 (X0)
/X1: JP1.6, JP9.6, U1.17 (X1)
/Y0: JP1.7, JP9.7, U1.18 (Y0)
/Y1: JP1.8, JP9.8, U1.19 (Y1)
GND: C1.2, C2.2, D1.1 (K), JP3.1, JP6.1, JP11.1, JP14.1, U1.33 (GND), U1.75 (GND)
unnamed: D1.2 (A), R1.2
VDD: C1.1, C2.1, JP6.3, JP14.3, R1.1, U1.77 (VDD)

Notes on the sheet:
Note: Schematic modified during KiCad 7 update. Rescued symbols were no longer available, so I made a best effort at replacing them.

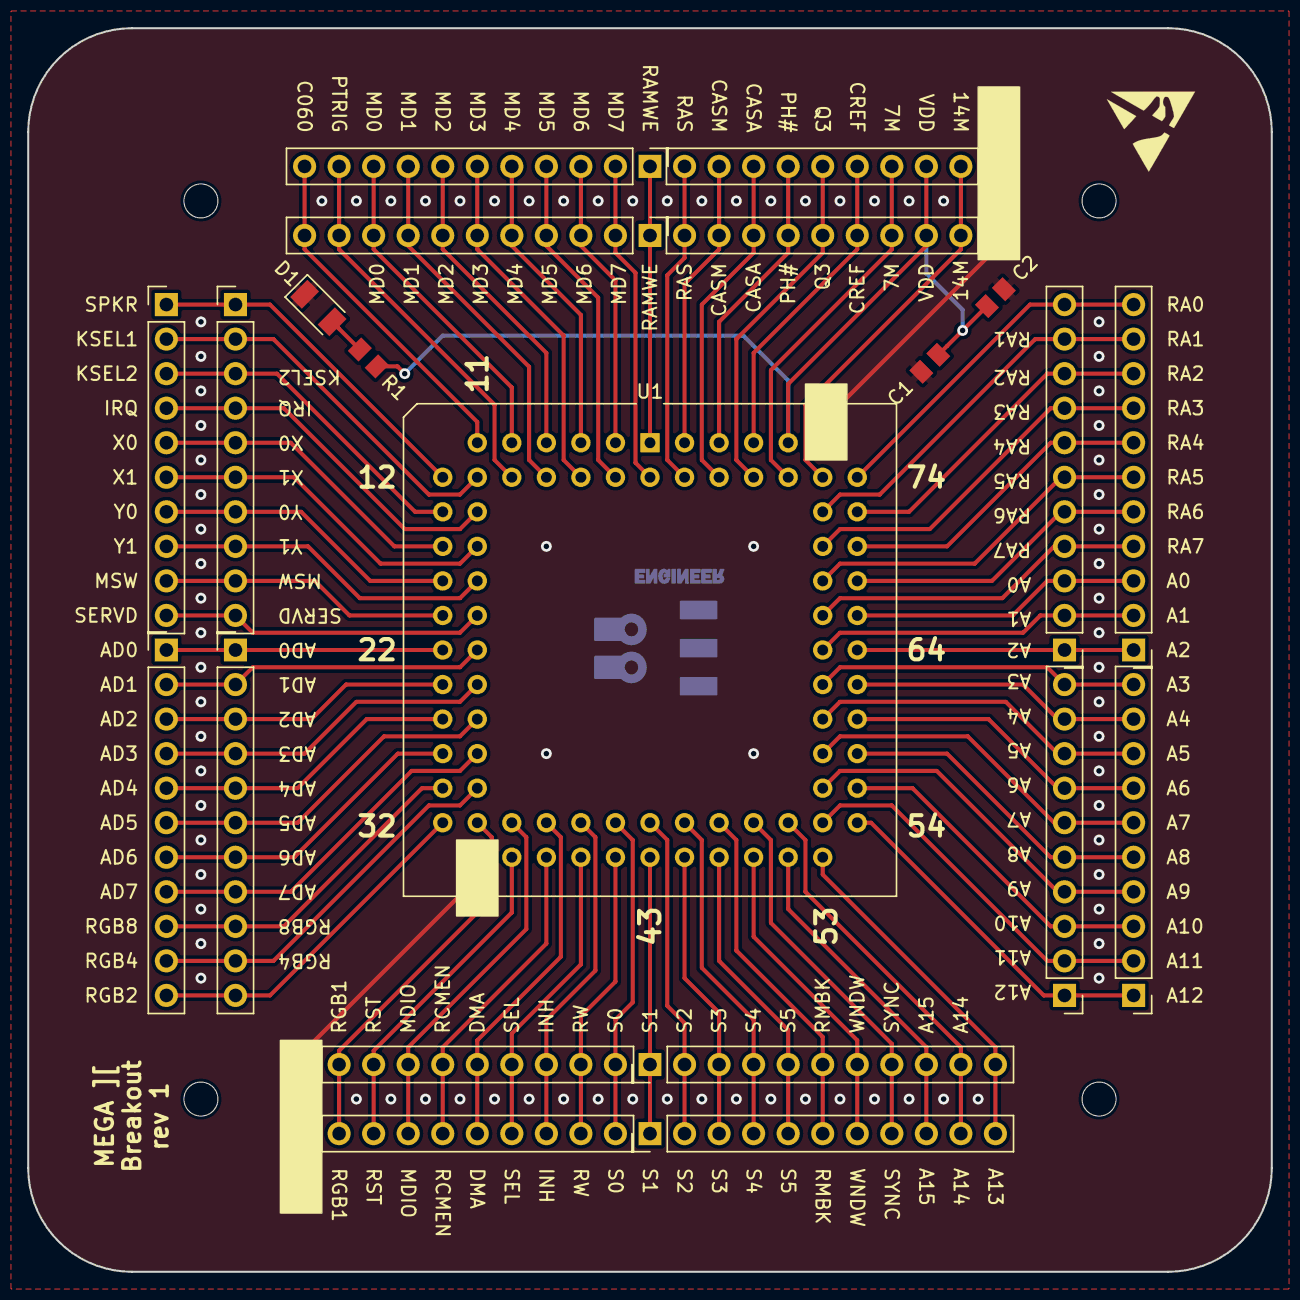
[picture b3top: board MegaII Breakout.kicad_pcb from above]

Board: 2 copper layers, 91.4 x 91.4 mm, 26 parts (1 on the bottom side), 84 nets.

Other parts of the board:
svg2mod: G***; BE10v2
